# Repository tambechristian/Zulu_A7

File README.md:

# Zulu A7

Zulu A7 is a USB FPGA board built around an AMD/Xilinx Artix-7
XC7A35T-2CPG236I. An FTDI FT2232HL bridge provides JTAG (channel A) and a
UART (channel B) over one micro-USB port. The board carries 64 MB of SDRAM,
a 128 Mbit quad-SPI configuration flash, a microSD socket, a Pmod host
header and a 40-pin breadboard header. It runs from USB through a
single-cell LiPo charger with power path and three buck regulators (3.3 V,
1.8 V and 1.0 V). The PCB is a 69.85 x 25.40 mm, six-layer HDI board.

The main design is the Altium Designer project in `Zulu_Altium_VS_Code/`.
Its fabrication and turnkey-assembly packages for PCBWay are dated
2026-10-07. Build and test results are not recorded in this repository.

## Origin and attribution

Zulu A7 is an adaptation of **XuLA2**, the USB FPGA prototyping board by
Dave Vandenbout / XESS Corp. (copyright 2012 XESS Corp.), published at
<https://github.com/xesscorp/XuLA2>. Its hardware design (schematic and
layout in `pcb/`) is licensed under
[CC BY-SA 3.0 Unported](https://creativecommons.org/licenses/by-sa/3.0/),
per the notice on its schematic. This repository does
not imply any connection with, or endorsement by, XESS Corp. or Dave
Vandenbout.

XESS's [product listing](https://www.tindie.com/products/xesscorp/xula2-lx25-fpga-prototyping-board/)
says the whole XuLA2 design was made open source and that anyone who
re-designs it must open-source their design too. As of 2026-10-07 it lists
XuLA2 as retired. The licence terms are those of CC BY-SA 3.0.

XuLA2 (schematic version 2.0, EAGLE 5 files) had a Xilinx Spartan-6
XC6SLX25 in FT256 and a Microchip PIC18F14K50 that handled reset and
initialisation, clock generation and USB-to-JTAG. It also had 256 Mbit
SDRAM, 8 Mbit SPI flash, a microSD socket, a mini-USB connector, ZLDO1117
3.3 V and 1.2 V regulators, a 40-pin breadboard prototyping header and an
aux JTAG header.

### Lineage

1. **XuLA2**: XESS Corp., 2012. The upstream design.
2. **XuLA3**: Christian Tambe's own rework of XuLA2, started 2026-08-10 in a
   separate local repository that is not published. It is not an XESS
   design. Its baseline is the XuLA2 schematic in EAGLE XML. The move to the
   Artix-7, the FT2232H bridge and an LTC3569 triple buck was made in XuLA3,
   before the fork. There the `xess` library was renamed `ctambe`, and the
   schematic AUTHOR and copyright line were changed to Christian Tambe.
3. **Zulu A7**: forked from XuLA3 on 2026-08-29 (commit `30a0e65`, "Zulu A7
   forks from XuLA3: the board is renamed, not redesigned"). That commit
   renamed X2's package XULA-DIP37 to ZULU-DIP37 and its deviceset XULA-CONN
   to ZULU-CONN, dropped unused devicesets including XC6SLX25-FT256 and
   PIC18F14K50, and set the version to 1.0. `zulu_a7.brd` took only its
   layer, settings and autorouter sections from the XuLA3 board;
   `tools/make_board.py` writes the geometry new.
4. **Altium and KiCad copies**: the EAGLE schematic was imported into Altium
   with the EAGLE Import Wizard in `Zulu_Altrium/` (commit `6d2efd6`).
   `Zulu_Altium_VS_Code/` is a later working copy of that project. The SC189
   regulators, the BQ24232 charger and the X2 pin field are Altium-side
   changes, and the board was routed there. `Zulu_kicad/` is a KiCad
   conversion of the Altium project.

### Main changes from XuLA2

| | XuLA2 | Zulu A7 |
|---|---|---|
| FPGA | Xilinx Spartan-6 XC6SLX25, FT256 | AMD/Xilinx Artix-7 XC7A35T-2CPG236I |
| USB bridge | Microchip PIC18F14K50 | FTDI FT2232HL with a 93LC46B EEPROM |
| USB connector | Hirose UX60SC-MB-5ST mini-USB | Molex 105017-0001 micro-USB |
| SDRAM | W9825G6JH-5, 256 Mbit | Alliance AS4C32M16SB-7TCN, 512 Mbit |
| Flash | W25Q80BV, 8 Mbit | Winbond W25Q128JV, 128 Mbit quad SPI |
| microSD | ALPS SCHD3A0100 | Hirose DM3D-SF |
| Clock | generated by the PIC18F14K50 | 12.000 MHz oscillator shared by the FT2232HL and the FPGA |
| Power | ZLDO1117 3.3 V and 1.2 V regulators | BQ24232 LiPo charger and three SC189 bucks (3.3 / 1.8 / 1.0 V) |
| Headers | 40-pin breadboard header, aux JTAG header | 40-pin breadboard header X2 with its own pin map, 2x6 Pmod host header J1, unpopulated JTAG holes JP3/JP4 |
| PCB | 2 in x 1 in | 69.85 x 25.40 mm, six-layer HDI |

XuLA3 and the EAGLE-era Zulu A7 used an LTC3569 triple buck. The Altium
copy replaced it on 2026-09-06 with the three SC189 bucks, so the EAGLE
files in this repository still show the LTC3569.

`docs/Zulu_A7-Design-Change-Record.html` lists the part changes from the
fork. Its "Was" column is the XuLA3 rev 1 state, which is mostly but not
entirely the XuLA2-LX25 BOM (the ESP8266 header and the BTN1 PTA-142 button
were XuLA3 additions). It predates the SC189 power section.

### What still comes from XuLA2

Compared with the `xess` library of the XuLA2 schematic (in its EAGLE XML
form), the `ctambe` library in the root `zulu_a7.sch` keeps 16 packages
byte-identical (for example TSOPII-54, SCHD3A0100, UX60SC-MB-5ST, CC_BY,
CC_CC and CC_COPYRIGHT), and 7 symbols and 5 devicesets are identical. The
later EAGLE copies keep the same packages with their keepout outlines
removed. Sheet text such as "Block Diagram",
"PROTOTYPING HEADER", "FPGA Connections" and the three licence lines is
kept verbatim. This material is in the EAGLE files (`zulu_a7.sch`,
`zulu_a7.brd` and the EAGLE copies in `Claude_Fable/`, `Zulu_Altrium/`,
`Zulu_Altium_VS_Code/` and `Altium_backup/`), in the SchDoc, PcbLib and
PcbDoc files of the four Altium copies and the September schematic PDFs,
and in `Zulu_kicad/kicad_project/` (`ctambe.kicad_sym`, footprints in
`zulu_a7.pretty/`, `zulu_a7.kicad_pcb` and `zulu_a7_2.kicad_sch`).

### Notices

In every copy of the schematic, the General IO sheet (sheet 3 of 7 in EAGLE
and Altium, `zulu_a7_2.SchDoc`; page 4 of 8 in KiCad, `zulu_a7_2.kicad_sch`,
under the added root sheet) carries "2026, Christian Tambe. Some rights
reserved." and the three CC BY-SA Unported licence lines, beside the CC
logos. The title block of every sheet reads "AUTHOR: Christian Tambe": in the
EAGLE files through the AUTHOR attribute, and in the Altium copies
(`Zulu_Altium_VS_Code/`, `Zulu_Altium_VS_Code_HDI_Optimized/`) and the KiCad
copy since 2026-10-08 (`Zulu_Altium_VS_Code/docs/schematic_author.md`). The
superseded `Zulu_Altrium/` and the `Altium_backup/` snapshot still show the
importer's placeholder "AUTHOR".
The upstream line "2012, XESS Corp. Some rights reserved." and the upstream
AUTHOR "Dave Vandenbout / XESS Corp." were replaced during the XuLA3 rework
and have never been in this repository's history, and the sheets do not yet
carry the XESS line again.
[LICENSE](LICENSE) reproduces the upstream notice and gives the credit for
XuLA2; keep it with any copy of the schematics.

## Board facts

- **FPGA**: U1 XC7A35T-2CPG236I, CPG236 BGA, 10 x 10 mm, 0.5 mm pitch.
- **USB**: U2 FTDI FT2232HL (LQFP-64). Channel A is MPSSE JTAG plus
  PROG#/DONE, channel B is the UART. U10 93LC46B configuration EEPROM.
  X1 Molex 105017-0001 micro-USB-B.
- **Memory**: U3 Alliance Memory AS4C32M16SB-7TCN, 512 Mbit (64 MB) SDRAM;
  the memory controller must use 10 column bits (A0-A9). U4 Winbond
  W25Q128JVSIQ, 128 Mbit quad SPI; the 17,536,096-bit bitstream leaves about
  14 MB for user data.
- **Clock**: Q1 ECS-3225SMV-120-FP-TR, 12.000 MHz, +-10 ppm HCMOS
  oscillator, driving the FT2232HL and the FPGA through 33 ohm each.
- **Power**: U8 TI BQ24232 single-cell LiPo charger with power path. Its
  output VU, the system rail that feeds the three bucks, is 4.4 V from USB
  and VBAT - 60 mV on battery; 495 mA input limit, 244 mA charge current.
  Battery on X4, a JST PH 2-pin header (pin 1 = battery +); the BOM has no
  battery. U5, U6 and U7 are Semtech SC189 bucks for 3.3 V, 1.8 V and 1.0 V
  (FPGA core).
- **I/O**: X2 40-pin breadboard header, 2.54 mm pitch, rows 22.86 mm apart,
  mounted from the underside; GND on pins 1, 17 and 21, +3.3 V on 18,
  +1.8 V on 19, +1.0 V on 20, VU on 22. J1 2x6 Pmod host header. X3 Hirose
  DM3D-SF microSD socket with card detect. JP3/JP4 unpopulated 1x3 JTAG
  holes. User button BTN, RGB LED LD0 and five 0603 LEDs (LD1-LD5).
- **PCB**: 69.85 x 25.40 mm, six layers (Top / L2 GND / L3 / L4 / L5 VCC3V3 /
  Bottom). Two-step HDI 1+1+N+1+1 with 0.15 mm laser microvias, 0.15 mm
  L3-L4 buried vias and 0.20 mm through vias. 3.0 / 3.5 mil minimum
  track / space. USB pair 90 ohm differential.
- **Status**: fully routed. Altium DRC on the final saved board (2026-10-07
  16:53) reports 0 violations; the report is
  `Zulu_Altium_VS_Code/Imported zulu_a7.PrjPcb/Design Rule Check - zulu_a7.drc`.
  The release packages identify the board by its PcbDoc SHA-256,
  `89a421b9060195d66bed82f7a4e7d80121bd0e9d679a3fee32289e8f541f4bde`.
- **Assembly**: 172 fitted designators (32 top, 140 bottom), 76 parts in
  0201. ENIG finish recommended. No fiducials on the board.

Known caveats, from `Zulu_Altium_VS_Code/docs/power_budget.md` and the
assembly notes:

- The worst-case draw (about 697 mA) exceeds the 495 mA input limit and needs
  the battery; with no battery the board browns out at that load. The board
  draws more than 100 mA before the FT2232HL enumerates.
- Every rail has more output capacitance than the SC189 datasheet's 30 uF
  start-up limit. Scope the three rails at power-on on the first board.
- LD0 green and blue are sunk from 3.3 V through 33 ohm and may be dim or
  dark; only red has margin.
- U5 and U7 look alike; swapping them puts 3.3 V on the FPGA core.

## Repository layout

| Entry | Status | Contents |
|---|---|---|
| `Zulu_Altium_VS_Code/` | **Current, authoritative** | Main Altium project: `Imported zulu_a7.PrjPcb/` (7 SchDocs, PcbDoc, PcbLib, released Gerber and NC-drill files, DRC report), `fabrication/`, `assembly/`, `docs/` (stage and decision records), `tools/`, `board/` (outline DXF; `JLCPCB-HDI-ENQUIRY.md` is superseded). The Stage-13 route plan is `tools/stage13/plan.json`; the root `plan.json` is a small XADC-knot plan. Its root `zulu_a7.sch` is the stale EAGLE import source. |
| `Zulu_Altium_VS_Code_HDI_Optimized/` | Derivative | Same-outline copy of the main board with 13 HDI sites turned into through vias, with its own fab zips and assembly release. |
| `Zulu_kicad/` | Derivative | KiCad 10 conversion of the main project, netlist-proven. Design rules were not translated, so KiCad DRC is not meaningful; do not refill zones. Altium stays the fabrication master. |
| `Zulu_Altrium/` | Superseded | Earlier Altium working copy: the EAGLE import, the September schematic work, routing placed through Stage 8 and the Stage 9-12 records (plans, never placed). Its PcbDoc is an intermediate Stage-13 Phase II board. |
| `Altium_backup/` | Snapshot | Backup of the Altium project taken during the September routing stages. |
| `Claude_Fable/` | Legacy | EAGLE/Fusion-era 8-layer HDI working copy, its board variants and tools. |
| `zulu_a7.sch` | Legacy | EAGLE schematic from the fork. It predates the released design (no BQ24232, no SC189) and is not the Altium import source, which is the later `Zulu_Altrium/zulu_a7.sch`. |
| `zulu_a7.brd` | Legacy | EAGLE board from the fork. |
| `tools/` | Legacy | EAGLE-era Python tools that read or write the root `zulu_a7.sch` / `zulu_a7.brd` (for example `make_board.py`, `validate.py`, `change_record.py`). |
| `board/` | Legacy | EAGLE/Fusion-era fab planning: `STACKUP.md`, EAGLE `.dru` rule files, DFM enquiry drafts, `pcbway/README.md`. Superseded by `Zulu_Altium_VS_Code/fabrication/PCBWAY_FAB_NOTES.txt`. |
| `docs/` | Mixed | `zulu_a7-bom.csv` is the current master BOM. `Zulu_A7-Design-Change-Record.html` is an EAGLE-era record. |
| `vivado/` | Mixed | `zulu_a7_pins.xdc` is current (Stage-13 pin permutation). `zulu_a7_io.rpt`, `zulu_a7_io.csv` and `zulu_a7_clocks.rpt` come from the 2026-09-10 Vivado run and show pre-swap balls; `zulu_a7_top.v` is the HDL top module used for that run. |
| `Zulu A7 Board Plan.html` | Legacy | Generated by `tools/board_plan.py`; shows the old 60.96 x 25.40 mm board. |
| `fix_sheet_names.cmd` | Legacy | EAGLE-era helper, run after exporting `zulu_a7.sch` from Fusion. |
| `W*P1.pdf`, `W*P2.pdf` | Vendor documents | PCBWay order-page printouts. They are not the fabrication spec; see `PCBWAY_FAB_NOTES.txt`. |
| `.gitignore` | | Ignores EAGLE and Vivado scratch files, `Datasheet/`, `board/*.pdf` and `archives/`. |

`archives/` and `Datasheet/` are ignored and are not part of the repository.

## Where to start

1. Open `Zulu_Altium_VS_Code/Imported zulu_a7.PrjPcb/zulu_a7.PrjPcb` in
   Altium Designer. The folder name comes from the EAGLE Import Wizard.
2. `Zulu_Altium_VS_Code/fabrication/PCBWAY_FAB_NOTES.txt`: what the current
   board is (stack, vias, impedance, outline, file map, final DRC).
3. `Zulu_Altium_VS_Code/assembly/Zulu_A7_Assembly_Notes.txt` and
   `Zulu_Altium_VS_Code/docs/pcbway_assembly_release.md`: the assembly
   release. To regenerate it, run
   `python tools/generate_jlcpcb_assembly.py --release-date 2026-10-07` from
   `Zulu_Altium_VS_Code/`.
4. `docs/zulu_a7-bom.csv`: the master BOM. Regenerate it only with
   `Zulu_Altium_VS_Code/tools/master_bom.py`; the copies in `Zulu_Altrium/`
   and `Altium_backup/` read stale sheets.
5. `Zulu_Altium_VS_Code/docs/power_budget.md`: power path, current budget
   and the caveats above.
   `Zulu_Altium_VS_Code/docs/stackup_impedance.md` gives the layer stack and the
   impedance of every routed trace width (`tools/stackup_impedance.py`).
6. `Zulu_Altium_VS_Code/docs/stage13_route_plan.md`, section "Final
   implementation closeout": how routing was finished. Later board changes
   are in `x1_slot_fix.md`, `x2_power_pins.md`, `x2_pin_labels.md` and
   `btn_move.md` in the same folder.
7. For FPGA work: `vivado/zulu_a7_pins.xdc` is the current pin map (the
   SDRAM ports need DRIVE 8, as set there). This repository has no
   programming instructions, FT2232H EEPROM image or example bitstream.
8. `Zulu_Altium_VS_Code_HDI_Optimized/HDI_OPTIMIZATION_NOTES.md` (the
   derivative board) and `Zulu_kicad/CONVERSION.md` (the KiCad copy).

Notes:

- No current schematic PDF is tracked. The `zulu_a7.pdf` files in
  `Zulu_Altrium/` and `Altium_backup/` are 2026-09-10 prints and are out of
  date.
- `Zulu_Altium_VS_Code/docs/` is a dated record of stages and decisions, and
  older entries describe superseded states. For example,
  `Zulu_Altium_VS_Code/docs/hdi_spec.md` and `board/pcbway/README.md` name
  JLCPCB as the fab. Where they disagree with the release files, the release
  files are current.
- `Zulu_Altium_VS_Code/tools/README.md` covers the import, schematic-edit and
  audit scripts (`pip install olefile pywin32`). It does not cover the
  routing toolkits or the assembly generator, which also needs `pymupdf` and
  `altium-monkey` (`pip install olefile pymupdf altium-monkey`).
- Vendor datasheets are not tracked. After a fresh clone, put AMD's package
  pinout file for the XC7A35T-CPG236 back as
  `Datasheet/xc7a35tcpg236pkg_pinout.txt`. Without it, `tools/validate.py`,
  `tools/vivado_io_check.py`, `tools/escape/rings.py` and
  `tools/change_record.py`, and the Altium copy's `tools/bom_audit.py`,
  `tools/connectivity_check.py` and `tools/stage13/xdc_check.py`, lose their
  ball checks or fail.

## Licence

See [LICENSE](LICENSE). Except for the third-party material listed there,
this repository, scripts included, is licensed under
[CC BY-SA 3.0 Unported](https://creativecommons.org/licenses/by-sa/3.0/legalcode).
It is an adaptation of XuLA2 (see above). Under section 8(b) of the licence,
XESS Corp., as Licensor of XuLA2, offers each recipient a licence to the
original XuLA2 Work on the same terms.

Design references, not files: some circuit choices follow Digilent's Cmod
A7. The SC189 bucks are "Cmod A7 style", the XADC input network is the one
Digilent uses on the Cmod A7, and the SDRAM, microSD and GPIO ball
assignments were first checked against the Cmod A7-35T. No Digilent file is
in this repository, and this licence grants nothing on Digilent's behalf.

Not in this repository: XuLA2's firmware (XESS code under GPL v2 or later,
plus Microchip USB-stack files under Microchip's licence), its FPGA example
designs (many files under GPL or LGPL), and the vendor datasheets and the
AMD/Xilinx pinout file (`Datasheet/` is ignored).

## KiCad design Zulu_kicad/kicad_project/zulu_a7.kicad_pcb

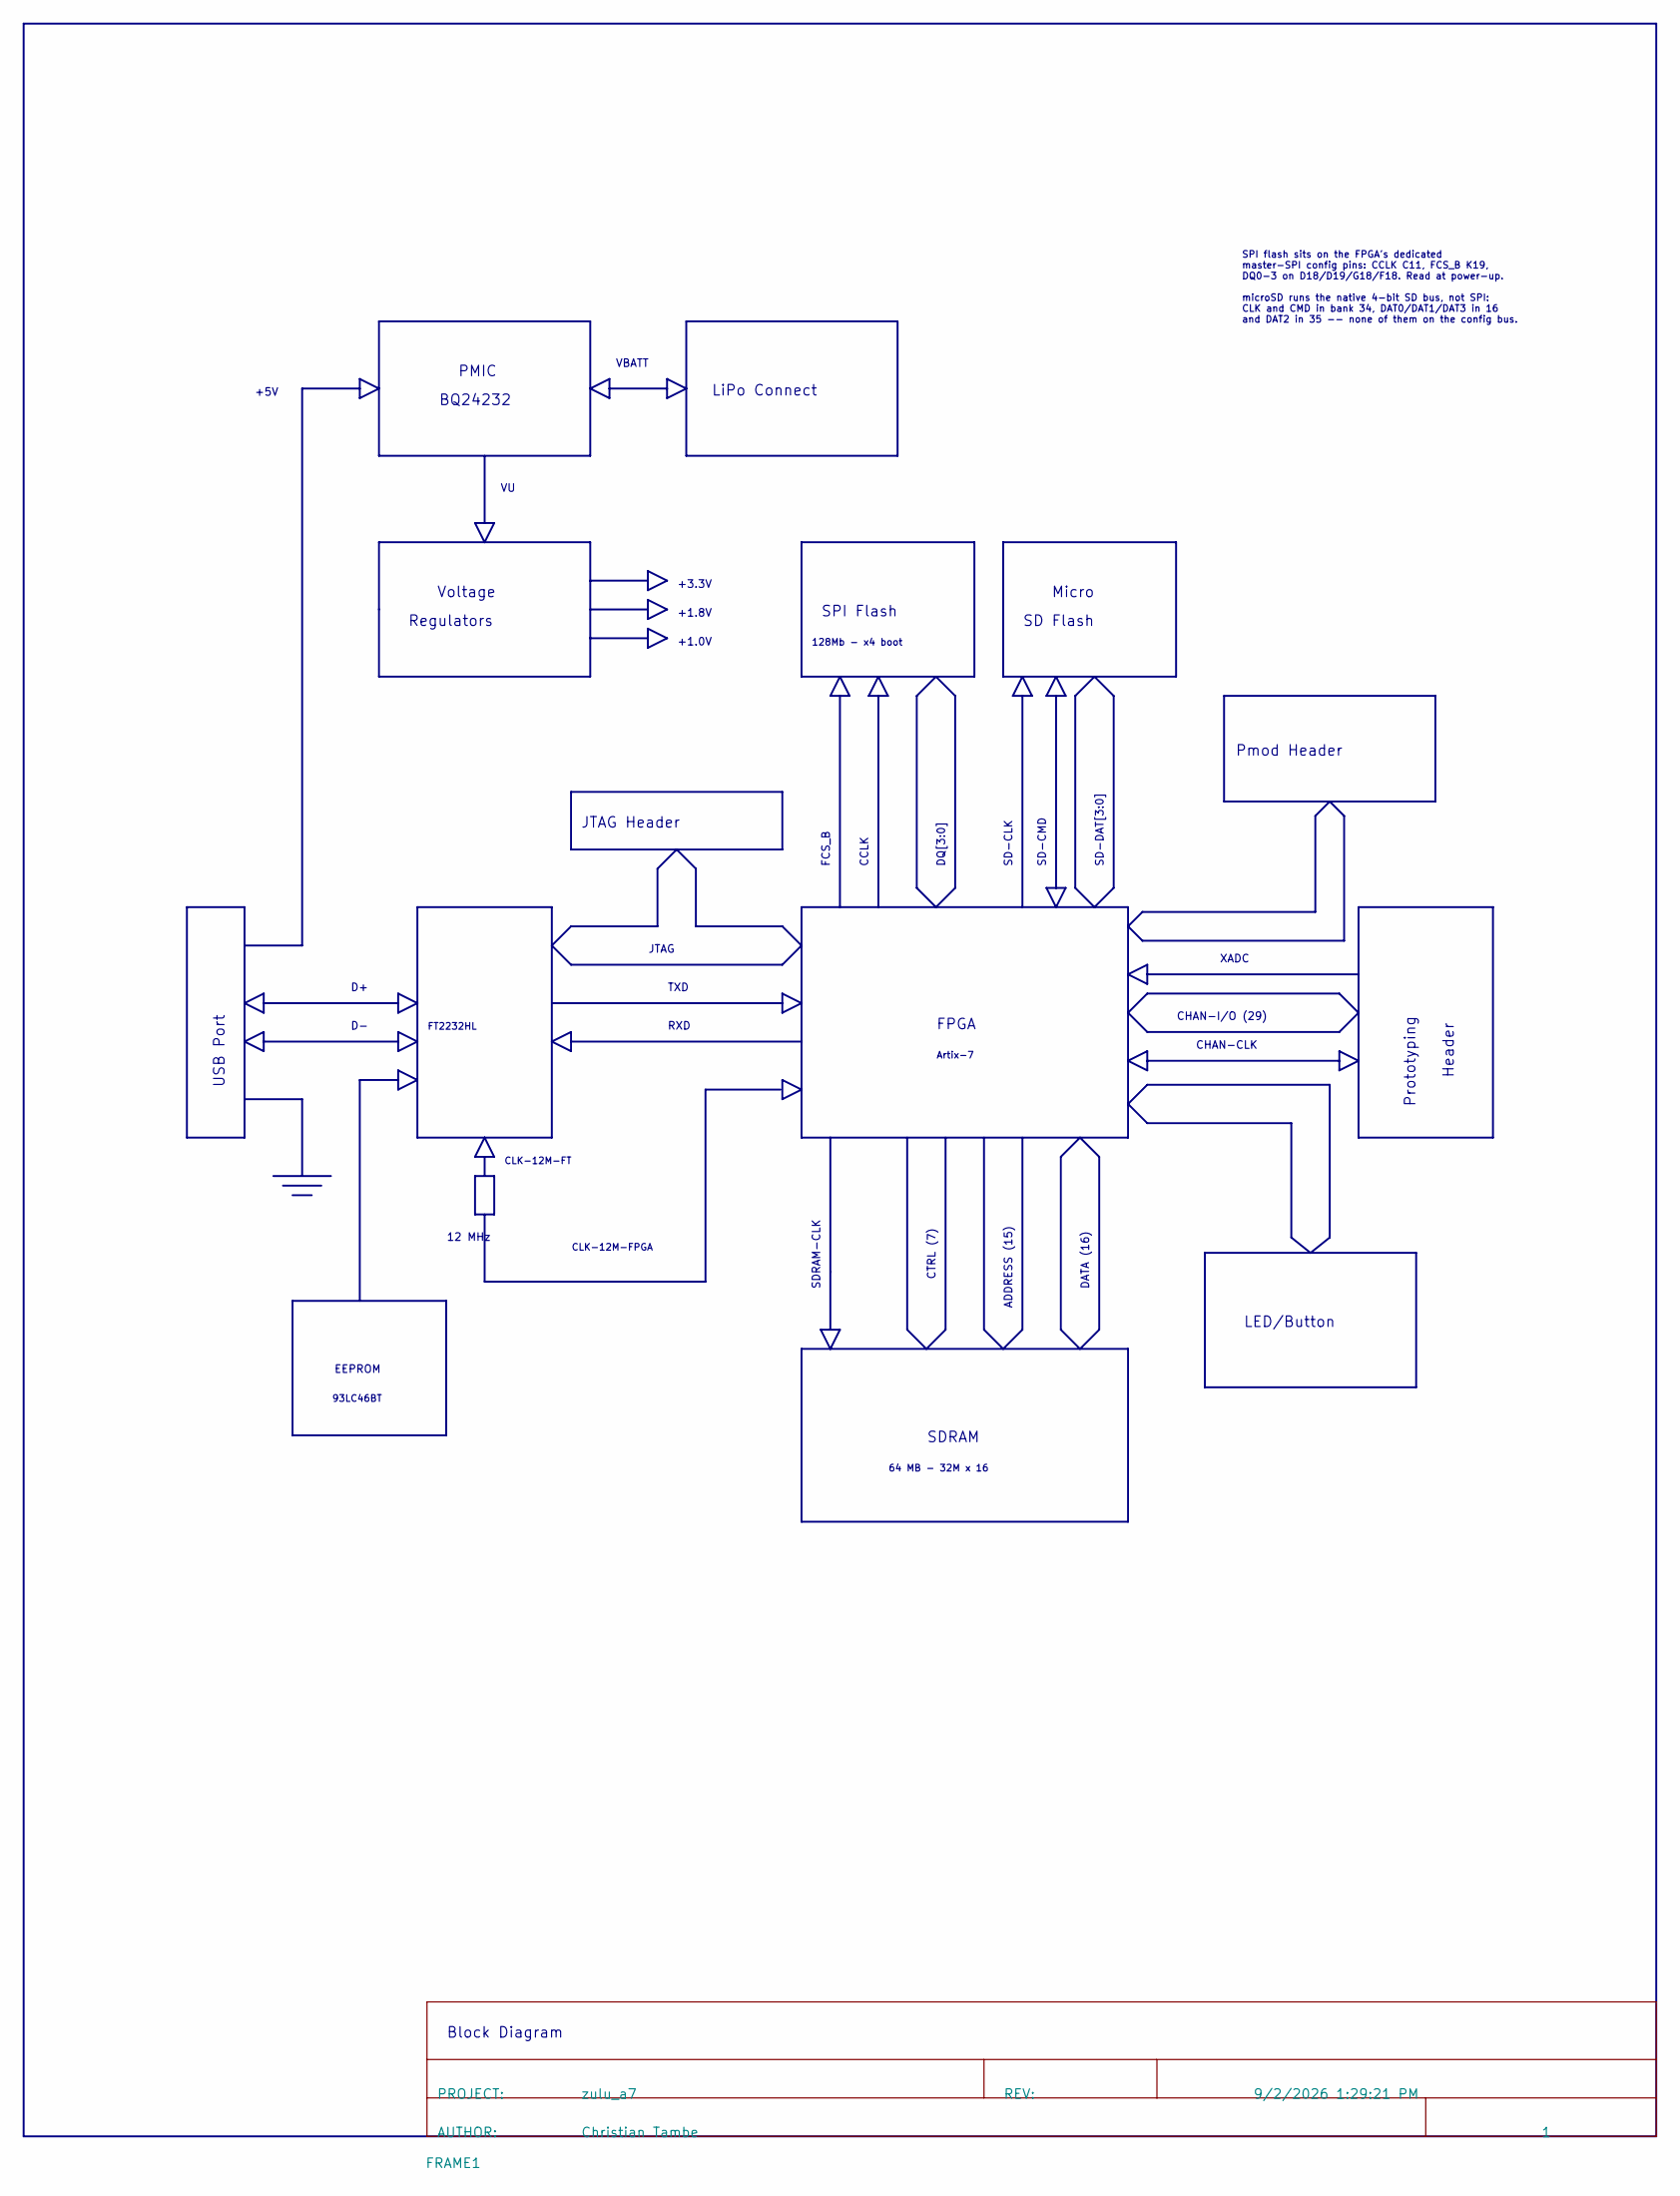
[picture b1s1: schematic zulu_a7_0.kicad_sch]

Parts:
FRAME1: DOCFIELD

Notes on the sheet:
Header
FPGA
SDRAM-CLK
FT2232HL
PMIC
SD-CMD
Prototyping
SD Flash
SD-DAT[3:0]
CLK-12M-FPGA
Voltage
SDRAM
FCS_B
Micro
JTAG
CTRL (7)
Block Diagram
93LC46BT
JTAG Header
CHAN-I/O (29)
+3.3V
CLK-12M-FT
LED/Button
DATA (16)
CHAN-CLK
Artix-7
XADC
ADDRESS (15)
128Mb - x4 boot
+5V
Pmod Header
DQ[3:0]
LiPo Connect
SD-CLK
RXD
TXD
+1.8V
12 MHz
+1.0V
CCLK

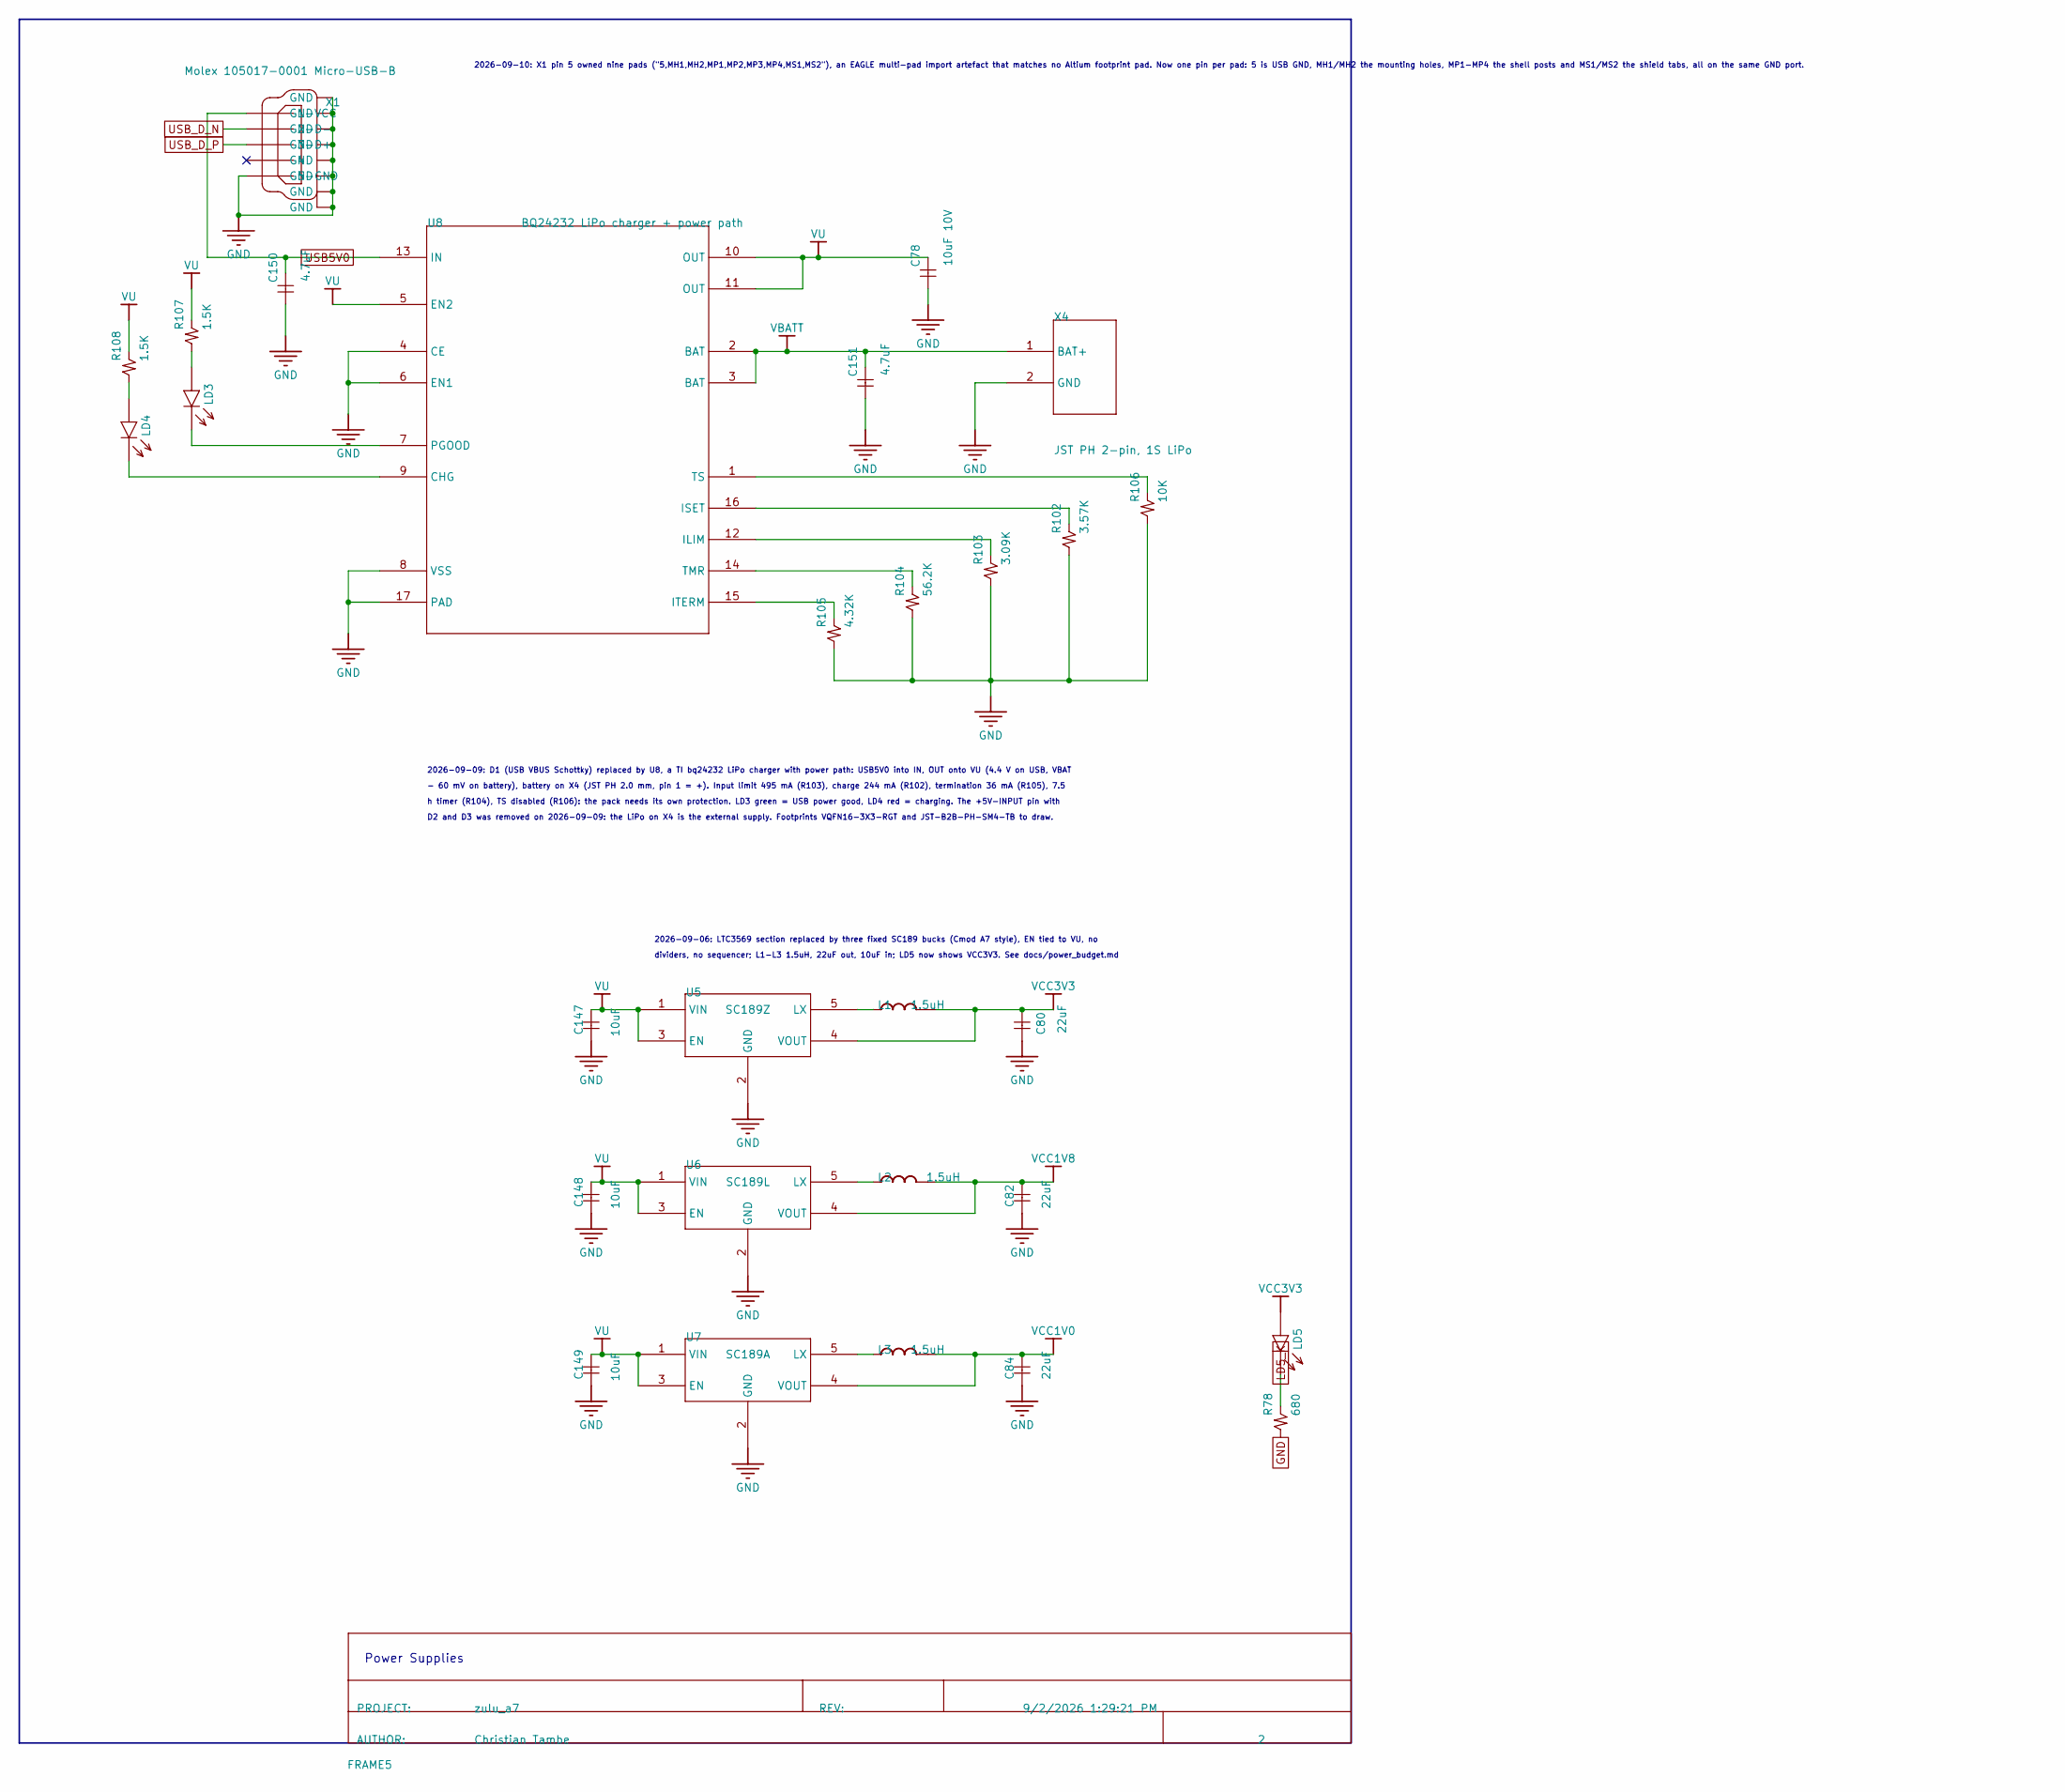
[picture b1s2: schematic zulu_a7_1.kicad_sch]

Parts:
C78: 10uF 10V; C0805
C80: 22uF; C0805
C82, C84: 22uF; C0603
C147, C148, C149: 10uF; C0805
C150, C151: 4.7uF; C0603
FRAME5: DOCFIELD
L1, L2, L3: 1.5uH; IND2520
LD3, LD5: green; LED0603
LD4: red; LED0603
R78: 680; R0402
R102: 3.57K; R0402
R103: 3.09K; R0402
R104: 56.2K; R0402
R105: 4.32K; R0402
R106: 10K; R0402
R107, R108: 1.5K; R0402
U5: SC189ZSKTRT; SOT23-5; PARTNAME SC189Z
U6: SC189LSKTRT; SOT23-5; PARTNAME SC189L
U7: SC189ASKTRT; SOT23-5; PARTNAME SC189A
U8: BQ24232 LiPo charger + power path; VQFN16-3X3-RGT
X1: Molex 105017-0001 Micro-USB-B; MOLEX-105017-0001
X4: JST PH 2-pin, 1S LiPo; JST-B2B-PH-SM4-TB

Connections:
GND: C78.1, C80.1, C82.1, C84.1, C147.1, C148.1, C149.1, C150.1, C151.1, R78.1, R102.1, R103.1, R104.1, R105.1, R106.1, U5.2 (GND), U6.2 (GND), U7.2 (GND), U8.4 (CE), U8.6 (EN1), U8.8 (VSS), U8.17 (PAD), X1.5 (5-GND), X1.MH1 (GND), X1.MH2 (GND), X1.MP1 (GND), X1.MP2 (GND), X1.MP3 (GND), X1.MP4 (GND), X1.MS1 (GND), X1.MS2 (GND), X4.2 (GND); also elsewhere on the board
LD5_K: LD5.K, R78.2
unnamed: LD3.A, R107.1
unnamed: LD4.A, R108.1
unnamed: L1.1, U5.5 (LX)
unnamed: L2.1, U6.5 (LX)
unnamed: L3.1, U7.5 (LX)
unnamed: LD4.K, U8.9 (CHG)
unnamed: R103.2, U8.12 (ILIM)
unnamed: R102.2, U8.16 (ISET)
unnamed: R105.2, U8.15 (ITERM)
unnamed: LD3.K, U8.7 (PGOOD)
unnamed: R104.2, U8.14 (TMR)
unnamed: R106.2, U8.1 (TS)
USB5V0: C150.2, U8.13 (IN), X1.1 (1-VCC)
USB_D_N: X1.2 (2-D-); also elsewhere on the board
USB_D_P: X1.3 (3-D+); also elsewhere on the board
VBATT: C151.2, U8.2 (BAT), U8.3 (BAT), X4.1 (BAT+)
VCC1V0: C84.2, L3.2, U7.4 (VOUT); also elsewhere on the board
VCC1V8: C82.2, L2.2, U6.4 (VOUT); also elsewhere on the board
VCC3V3: C80.2, L1.2, LD5.A, U5.4 (VOUT); also elsewhere on the board
VU: C78.2, C147.2, C148.2, C149.2, R107.2, R108.2, U5.1 (VIN), U5.3 (EN), U6.1 (VIN), U6.3 (EN), U7.1 (VIN), U7.3 (EN), U8.5 (EN2), U8.10 (OUT), U8.11 (OUT); also elsewhere on the board

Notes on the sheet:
2026-09-06: LTC3569 section replaced by three fixed SC189 bucks (Cmod A7 style), EN tied to VU, no
Power Supplies
2026-09-09: D1 (USB VBUS Schottky) replaced by U8, a TI bq24232 LiPo charger with power path: USB5V0 into IN, OUT onto VU (4.4 V on USB, VBAT
- 60 mV on battery), battery on X4 (JST PH 2.0 mm, pin 1 = +). Input limit 495 mA (R103), charge 244 mA (R102), termination 36 mA (R105), 7.5
2026-09-10: X1 pin 5 owned nine pads ("5,MH1,MH2,MP1,MP2,MP3,MP4,MS1,MS2"), an EAGLE multi-pad import artefact that matches no Altium footprint pad. Now one pin per pad: 5 is USB GND, MH1/MH2 the mounting holes, MP1-MP4 the shell posts and MS1/MS2 the shield tabs, all on the same GND port.
dividers, no sequencer; L1-L3 1.5uH, 22uF out, 10uF in; LD5 now shows VCC3V3. See docs/power_budget.md
D2 and D3 was removed on 2026-09-09: the LiPo on X4 is the external supply. Footprints VQFN16-3X3-RGT and JST-B2B-PH-SM4-TB to draw.
h timer (R104), TS disabled (R106): the pack needs its own protection. LD3 green = USB power good, LD4 red = charging. The +5V-INPUT pin with

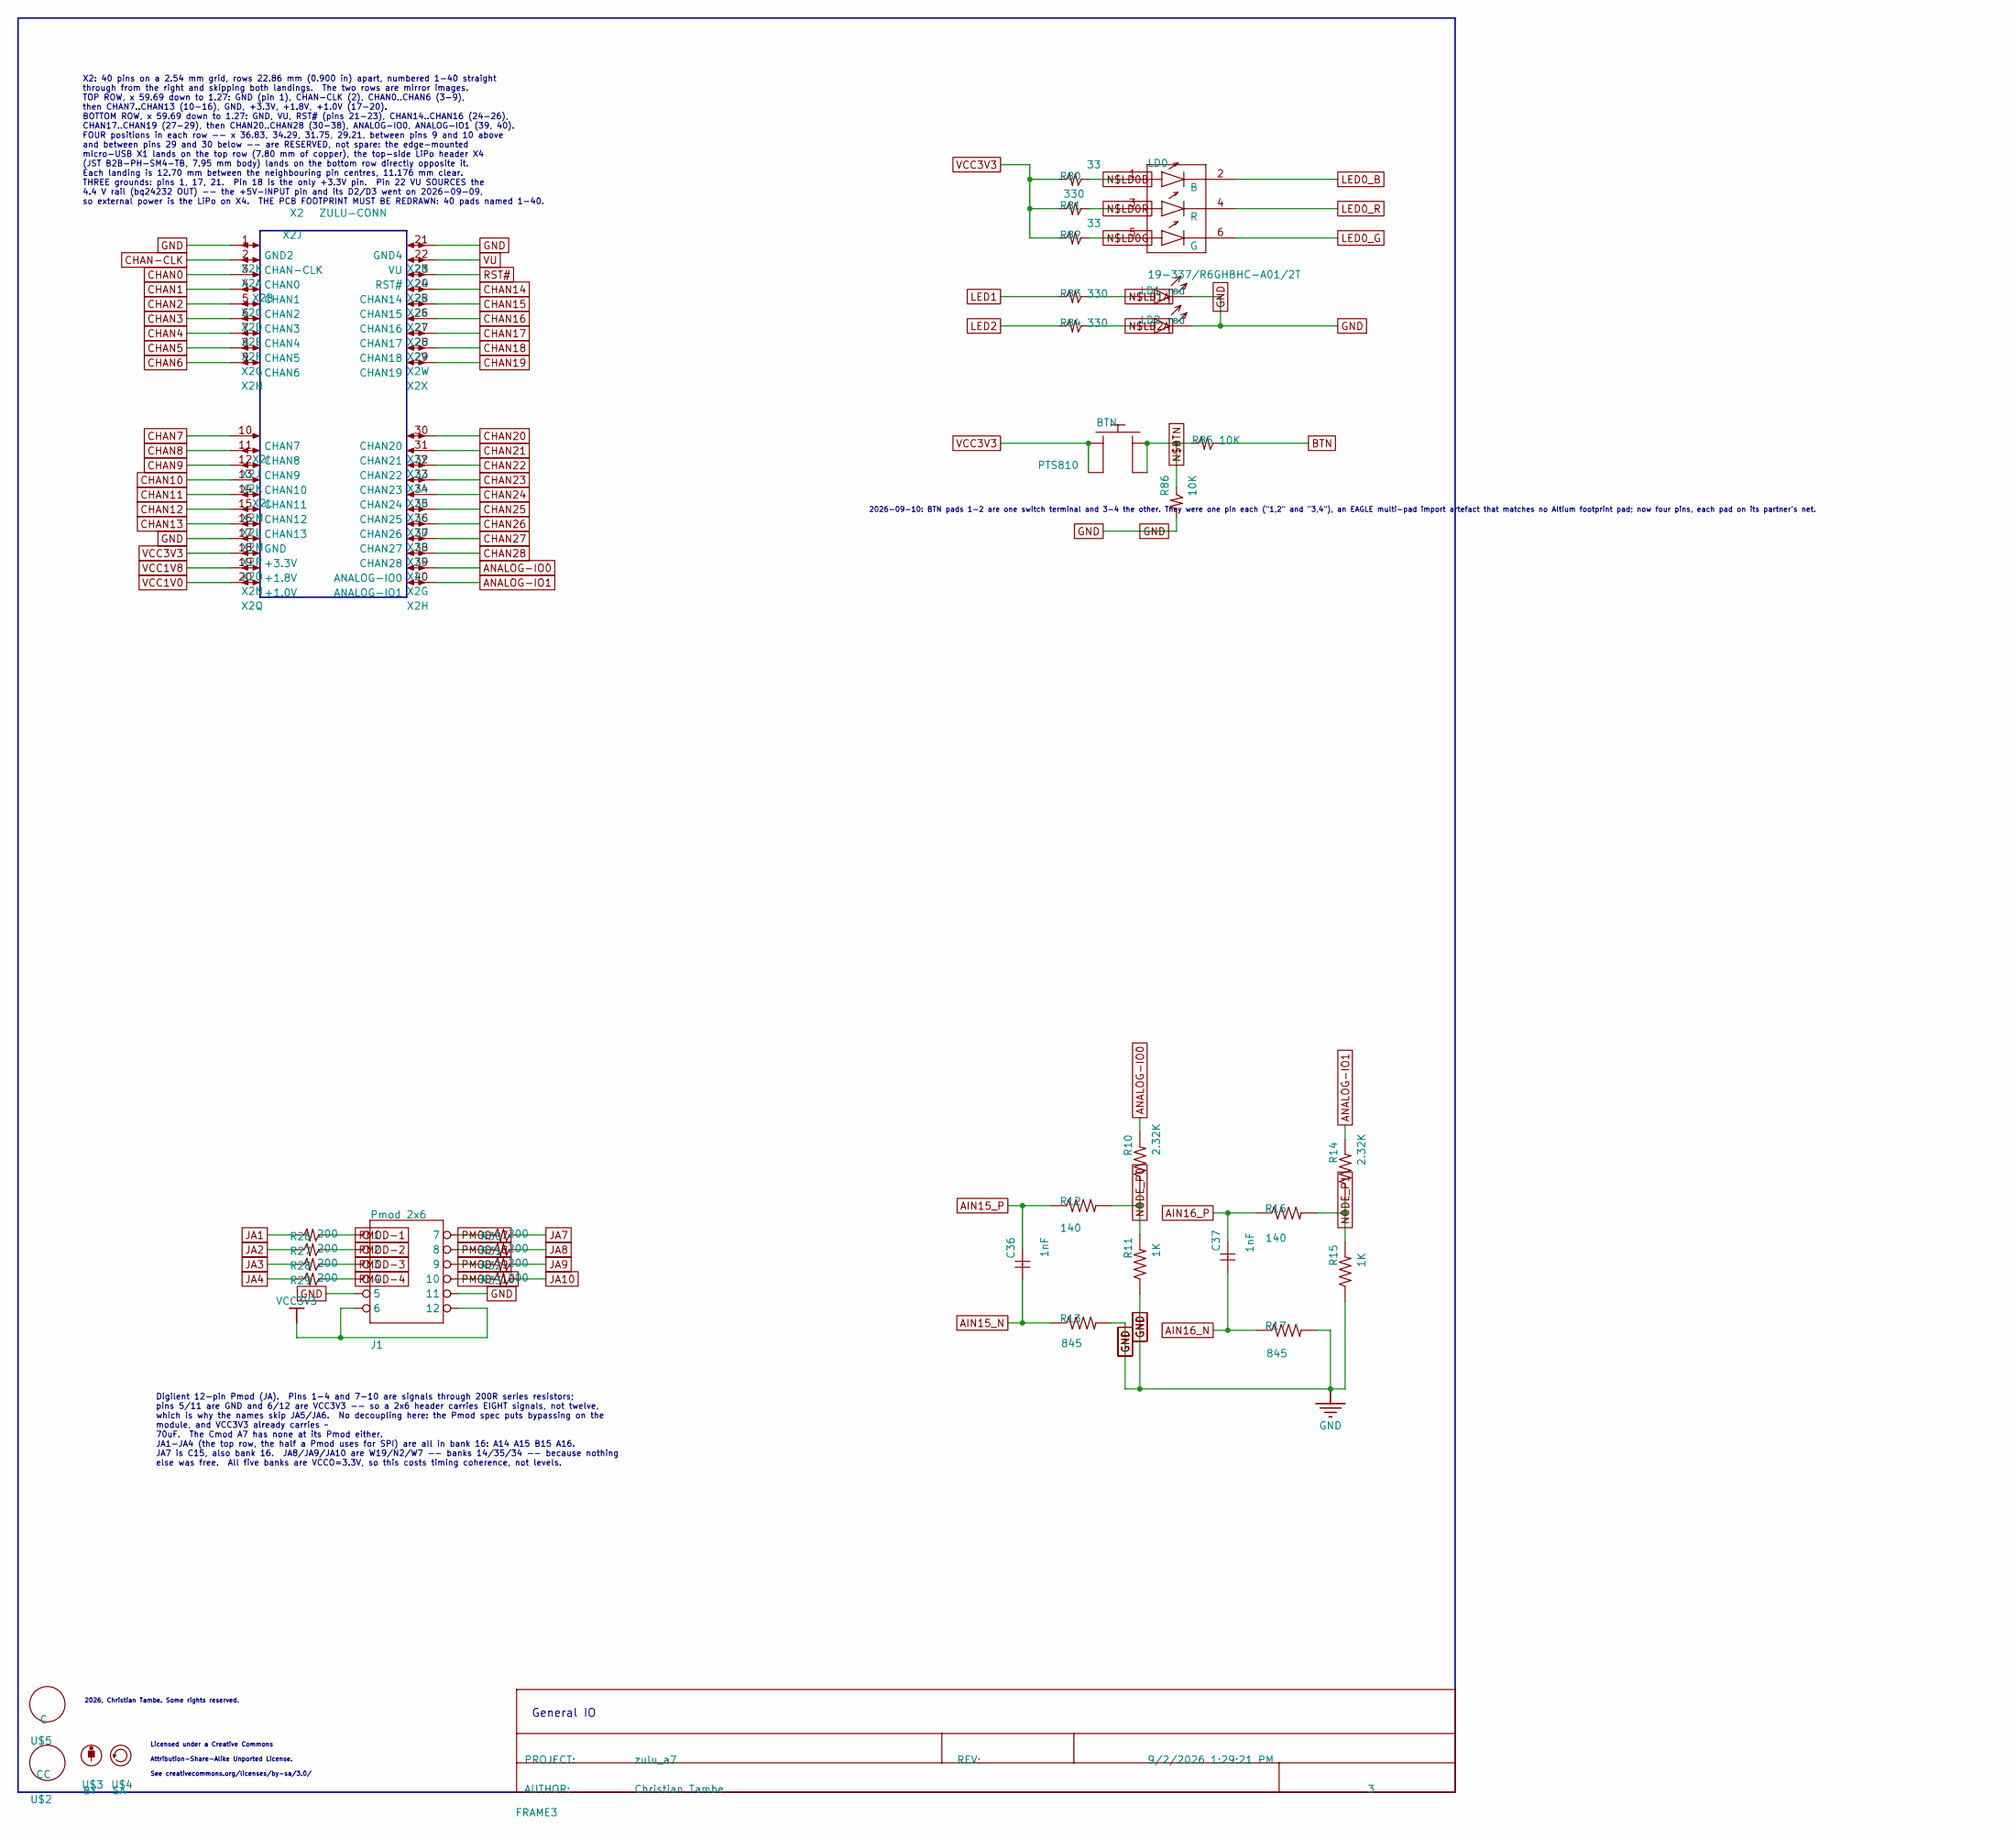
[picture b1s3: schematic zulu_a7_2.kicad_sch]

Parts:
BTN: PTS810
C36, C37: 1nF; C0402
FRAME3: DOCFIELD
J1: Pmod 2x6; 2X06
LD0: 19-337/R6GHBHC-A01/2T; EVERLIGHT-19-337
LD1, LD2: red; LED0603
R10, R14: 2.32K; R0201
R11, R15: 1K; R0201
R12, R16: 140; R0201
R13, R17: 845; R0201
R26, R27, R28, R29, R30, R31, R32, R33: 200; R0201
R80, R82: 33; R0402
R81, R83, R84: 330; R0402
R85, R86: 10K; R0402
U$2: CC_CC
U$3: CC_BY
U$4: CC_SA
U$5: CC_COPYRIGHT
X2: ZULU-CONN; ZULU-DIP37

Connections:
AIN15_N: C36.1, R13.1; also elsewhere on the board
AIN15_P: C36.2, R12.1; also elsewhere on the board
AIN16_N: C37.1, R17.1; also elsewhere on the board
AIN16_P: C37.2, R16.1; also elsewhere on the board
ANALOG-IO0: R10.2, X2.39
ANALOG-IO1: R14.2, X2.40
BTN: R85.2; also elsewhere on the board
CHAN0: X2.3; also elsewhere on the board
CHAN1: X2.4; also elsewhere on the board
CHAN2: X2.5; also elsewhere on the board
CHAN3: X2.6; also elsewhere on the board
CHAN4: X2.7; also elsewhere on the board
CHAN5: X2.8; also elsewhere on the board
CHAN6: X2.9; also elsewhere on the board
CHAN7: X2.10; also elsewhere on the board
CHAN8: X2.11; also elsewhere on the board
CHAN9: X2.12; also elsewhere on the board
CHAN10: X2.13; also elsewhere on the board
CHAN11: X2.14; also elsewhere on the board
CHAN12: X2.15; also elsewhere on the board
CHAN13: X2.16; also elsewhere on the board
CHAN14: X2.24; also elsewhere on the board
CHAN15: X2.25; also elsewhere on the board
CHAN16: X2.26; also elsewhere on the board
CHAN17: X2.27; also elsewhere on the board
CHAN18: X2.28; also elsewhere on the board
CHAN19: X2.29; also elsewhere on the board
CHAN20: X2.30; also elsewhere on the board
CHAN21: X2.31; also elsewhere on the board
CHAN22: X2.32; also elsewhere on the board
CHAN23: X2.33; also elsewhere on the board
CHAN24: X2.34; also elsewhere on the board
CHAN25: X2.35; also elsewhere on the board
CHAN26: X2.36; also elsewhere on the board
CHAN27: X2.37; also elsewhere on the board
CHAN28: X2.38; also elsewhere on the board
CHAN-CLK: X2.2; also elsewhere on the board
GND: J1.5, J1.11, LD1.K, LD2.K, R11.1, R13.2, R15.1, R17.2, R86.1, X2.1, X2.17, X2.21; also elsewhere on the board
JA1: R26.1; also elsewhere on the board
JA2: R27.1; also elsewhere on the board
JA3: R28.1; also elsewhere on the board
JA4: R29.1; also elsewhere on the board
JA7: R30.2; also elsewhere on the board
JA8: R31.2; also elsewhere on the board
JA9: R32.2; also elsewhere on the board
JA10: R33.2; also elsewhere on the board
LED0_B: LD0.2; also elsewhere on the board
LED0_G: LD0.6; also elsewhere on the board
LED0_R: LD0.4; also elsewhere on the board
LED1: R83.1; also elsewhere on the board
LED2: R84.1; also elsewhere on the board
N$BTN: BTN.3 (2), BTN.4 (2), R85.1, R86.2
N$LD0B: LD0.1, R80.2
N$LD0G: LD0.5, R82.2
N$LD0R: LD0.3, R81.2
N$LD1A: LD1.A, R83.2
N$LD2A: LD2.A, R84.2
NODE_P0: R10.1, R11.2, R12.2
NODE_P1: R14.1, R15.2, R16.2
PMOD-1: J1.1, R26.2
PMOD-2: J1.2, R27.2
PMOD-3: J1.3, R28.2
PMOD-4: J1.4, R29.2
PMOD-7: J1.7, R30.1
PMOD-8: J1.8, R31.1
PMOD-9: J1.9, R32.1
PMOD-10: J1.10, R33.1
RST#: X2.23; also elsewhere on the board
VCC1V0: X2.20; also elsewhere on the board
VCC1V8: X2.19; also elsewhere on the board
VCC3V3: BTN.1, BTN.2 (1), J1.6, J1.12, R80.1, R81.1, R82.1, X2.18; also elsewhere on the board
VU: X2.22; also elsewhere on the board

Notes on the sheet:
Licensed under a Creative Commons
See creativecommons.org/licenses/by-sa/3.0/
General IO
2026-09-10: BTN pads 1-2 are one switch terminal and 3-4 the other. They were one pin each ("1,2" and "3,4"), an EAGLE multi-pad import artefact that matches no Altium footprint pad; now four pins, each pad on its partner's net.
Attribution-Share-Alike Unported License.
2026, Christian Tambe. Some rights reserved.
Digilent 12-pin Pmod (JA). Pins 1-4 and 7-10 are signals through 200R series resistors; pins 5/11 are GND and 6/12 are VCC3V3 -- so a 2x6 header carries EIGHT signals, not twelve, which is why the names skip JA5/JA6. No decoupling here: the Pmod spec puts bypassing on the module, and VCC3V3 already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
X2: 40 pins on a 2.54 mm grid, rows 22.86 mm (0.900 in) apart, numbered 1-40 straight through from the right and skipping both landings. The two rows are mirror images. TOP ROW, x 59.69 down to 1.27: GND (pin 1), CHAN-CLK (2), CHAN0..CHAN6 (3-9), then CHAN7..CHAN13 (10-16), GND, +3.3V, +1.8V, +1.0V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
